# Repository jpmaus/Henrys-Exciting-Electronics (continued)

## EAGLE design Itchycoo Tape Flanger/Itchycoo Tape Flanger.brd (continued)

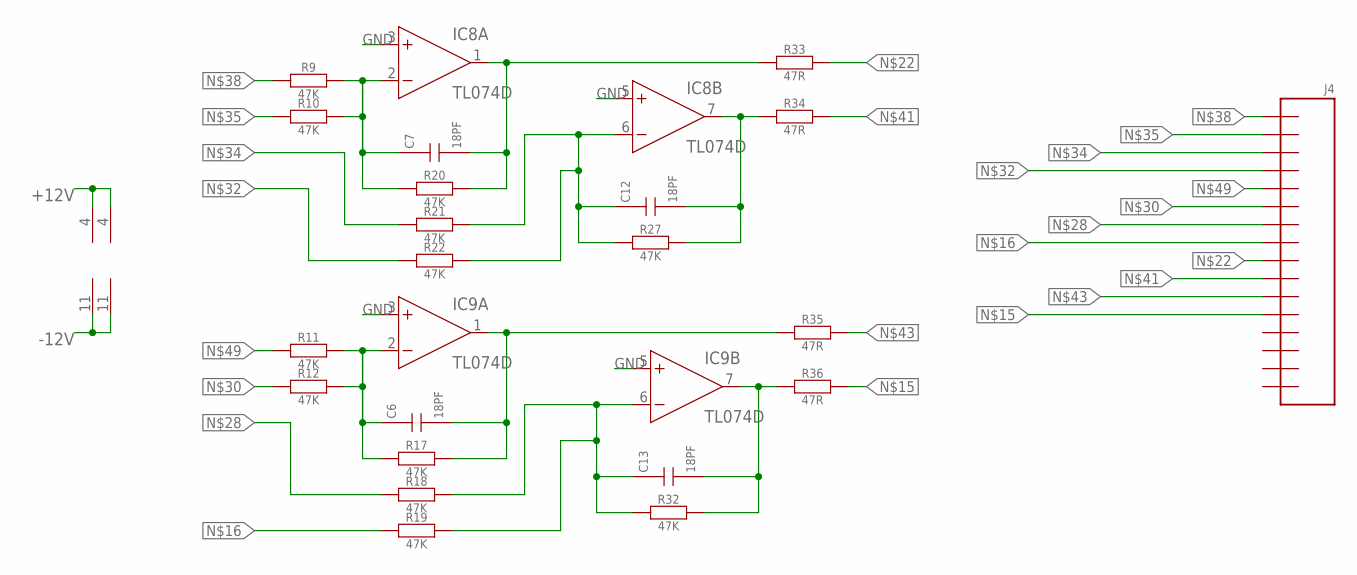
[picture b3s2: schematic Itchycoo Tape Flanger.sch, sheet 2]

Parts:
C6, C7, C12, C13: 18PF; CT6032
IC8, IC9: TL074D; SO14
J4: CON_16; 2X08SMT
R9, R10, R11, R12, R17, R18, R19, R20, R21, R22, R27, R32: 47K; R6332W
R33, R34, R35, R36: 47R; R6332W

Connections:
+12V: IC8.4 (V+), IC9.4 (V+); also elsewhere on the board
-12V: IC8.11 (V-), IC9.11 (V-); also elsewhere on the board
GND: IC8.3 (+IN), IC8.5 (+IN), IC9.3 (+IN), IC9.5 (+IN); also elsewhere on the board
unnamed: J4.12, R36.2
unnamed: J4.8, R19.1
unnamed: J4.9, R33.2
unnamed: J4.7, R18.1
unnamed: J4.6, R12.1
unnamed: J4.4, R22.1
unnamed: J4.3, R21.1
unnamed: J4.2, R10.1
unnamed: C7.+ (1), IC8.2 (-IN), R9.2, R10.2, R20.1
unnamed: C7.- (2), IC8.1 (OUT), R20.2, R33.1
unnamed: J4.1, R9.1
unnamed: C12.- (2), IC8.7 (OUT), R27.2, R34.1
unnamed: J4.10, R34.2
unnamed: J4.11, R35.2
unnamed: J4.5, R11.1
unnamed: C12.+ (1), IC8.6 (-IN), R21.2, R22.2, R27.1
unnamed: C6.+ (1), IC9.2 (-IN), R11.2, R12.2, R17.1
unnamed: C6.- (2), IC9.1 (OUT), R17.2, R35.1
unnamed: C13.- (2), IC9.7 (OUT), R32.2, R36.1
unnamed: C13.+ (1), IC9.6 (-IN), R18.2, R19.2, R32.1

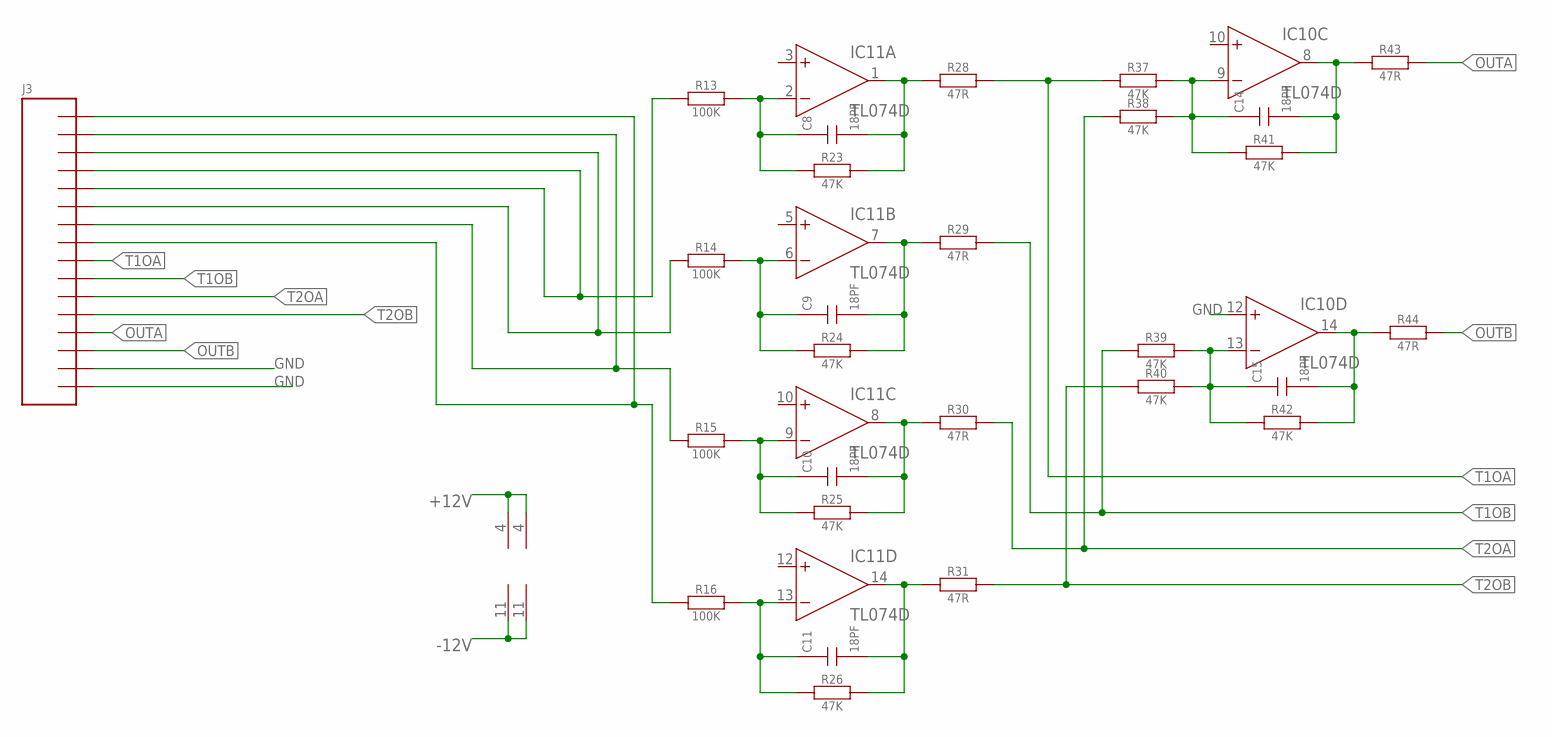
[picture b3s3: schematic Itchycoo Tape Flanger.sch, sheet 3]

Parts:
C8, C9, C10, C11, C14, C15: 18PF; CT6032
IC10, IC11: TL074D; SO14
J3: CON_16; 2X08SMT
R13, R14, R15, R16: 100K; R6332W
R23, R24, R25, R26, R37, R38, R39, R40, R41, R42: 47K; R6332W
R28, R29, R30, R31, R43, R44: 47R; R6332W

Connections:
+12V: IC10.4 (V+), IC11.4 (V+); also elsewhere on the board
-12V: IC10.11 (V-), IC11.11 (V-); also elsewhere on the board
GND: IC10.12 (+IN), J3.15, J3.16; also elsewhere on the board
unnamed: J3.4, J3.5, R13.1
unnamed: C8.- (2), IC11.1 (OUT), R23.2, R28.1
unnamed: J3.3, J3.6, R14.1
unnamed: J3.2, J3.7, R15.1
unnamed: J3.1, J3.8, R16.1
unnamed: C9.+ (1), IC11.6 (-IN), R14.2, R24.1
unnamed: C9.- (2), IC11.7 (OUT), R24.2, R29.1
unnamed: C10.+ (1), IC11.9 (-IN), R15.2, R25.1
unnamed: C10.- (2), IC11.8 (OUT), R25.2, R30.1
unnamed: C11.- (2), IC11.14 (OUT), R26.2, R31.1
unnamed: C11.+ (1), IC11.13 (-IN), R16.2, R26.1
unnamed: C8.+ (1), IC11.2 (-IN), R13.2, R23.1
unnamed: C14.+ (1), IC10.9 (-IN), R37.2, R38.2, R41.1
unnamed: C14.- (2), IC10.8 (OUT), R41.2, R43.1
unnamed: C15.+ (1), IC10.13 (-IN), R39.2, R40.2, R42.1
unnamed: C15.- (2), IC10.14 (OUT), R42.2, R44.1
OUTA: J3.13, R43.2
OUTB: J3.14, R44.2
T1OA: J3.9, R28.2, R37.1
T1OB: J3.10, R29.2, R39.1
T2OA: J3.11, R30.2, R38.1
T2OB: J3.12, R31.2, R40.1

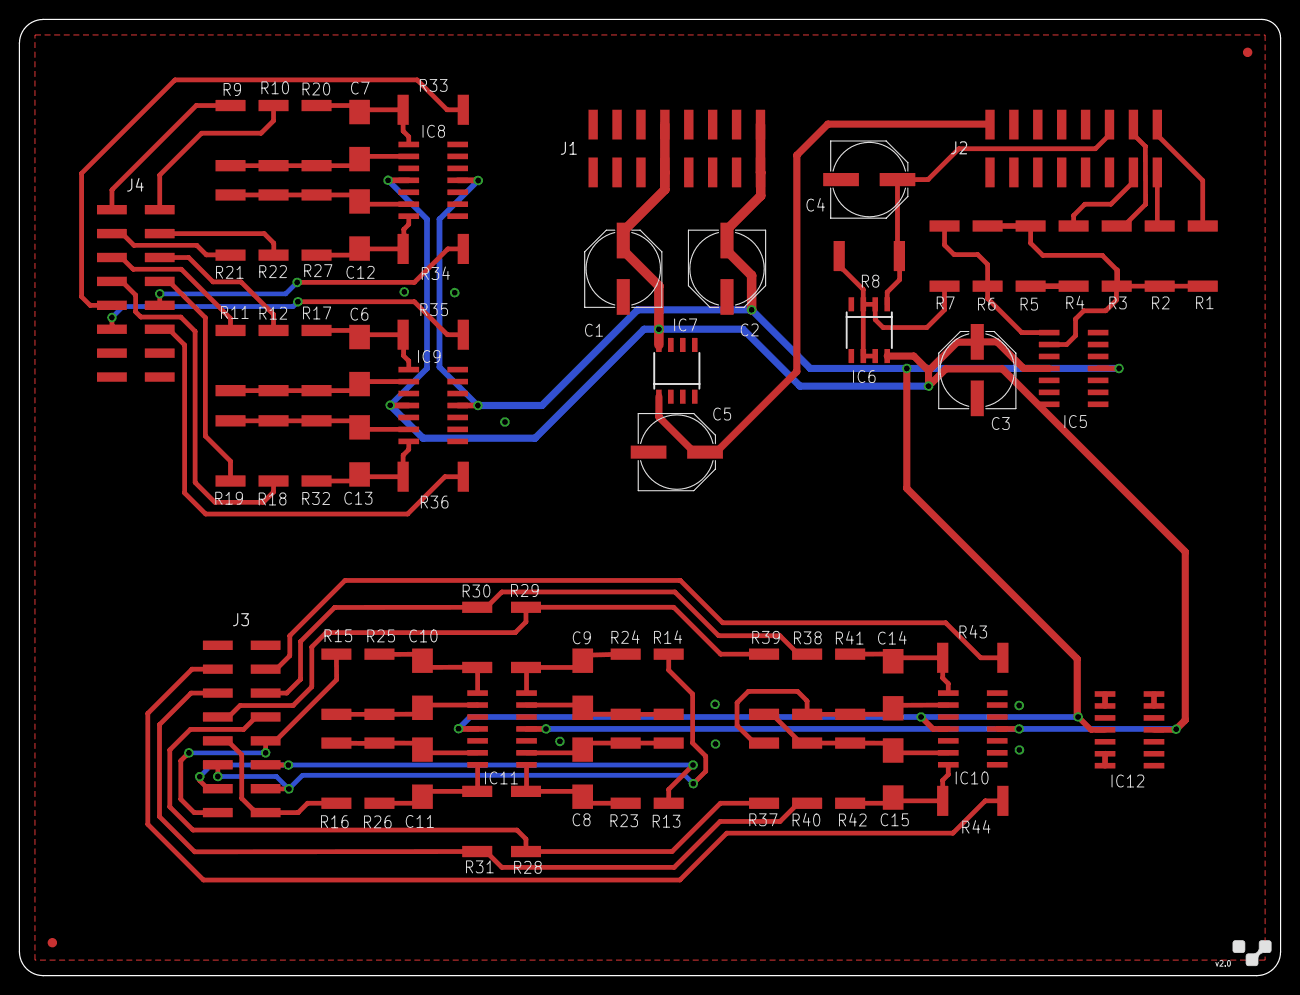
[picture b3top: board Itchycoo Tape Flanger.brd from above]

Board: 2 copper layers, 134.0 x 101.6 mm, 72 parts (0 on the bottom side), 58 nets.

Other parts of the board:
E$1: 4X5_BOARD_V2

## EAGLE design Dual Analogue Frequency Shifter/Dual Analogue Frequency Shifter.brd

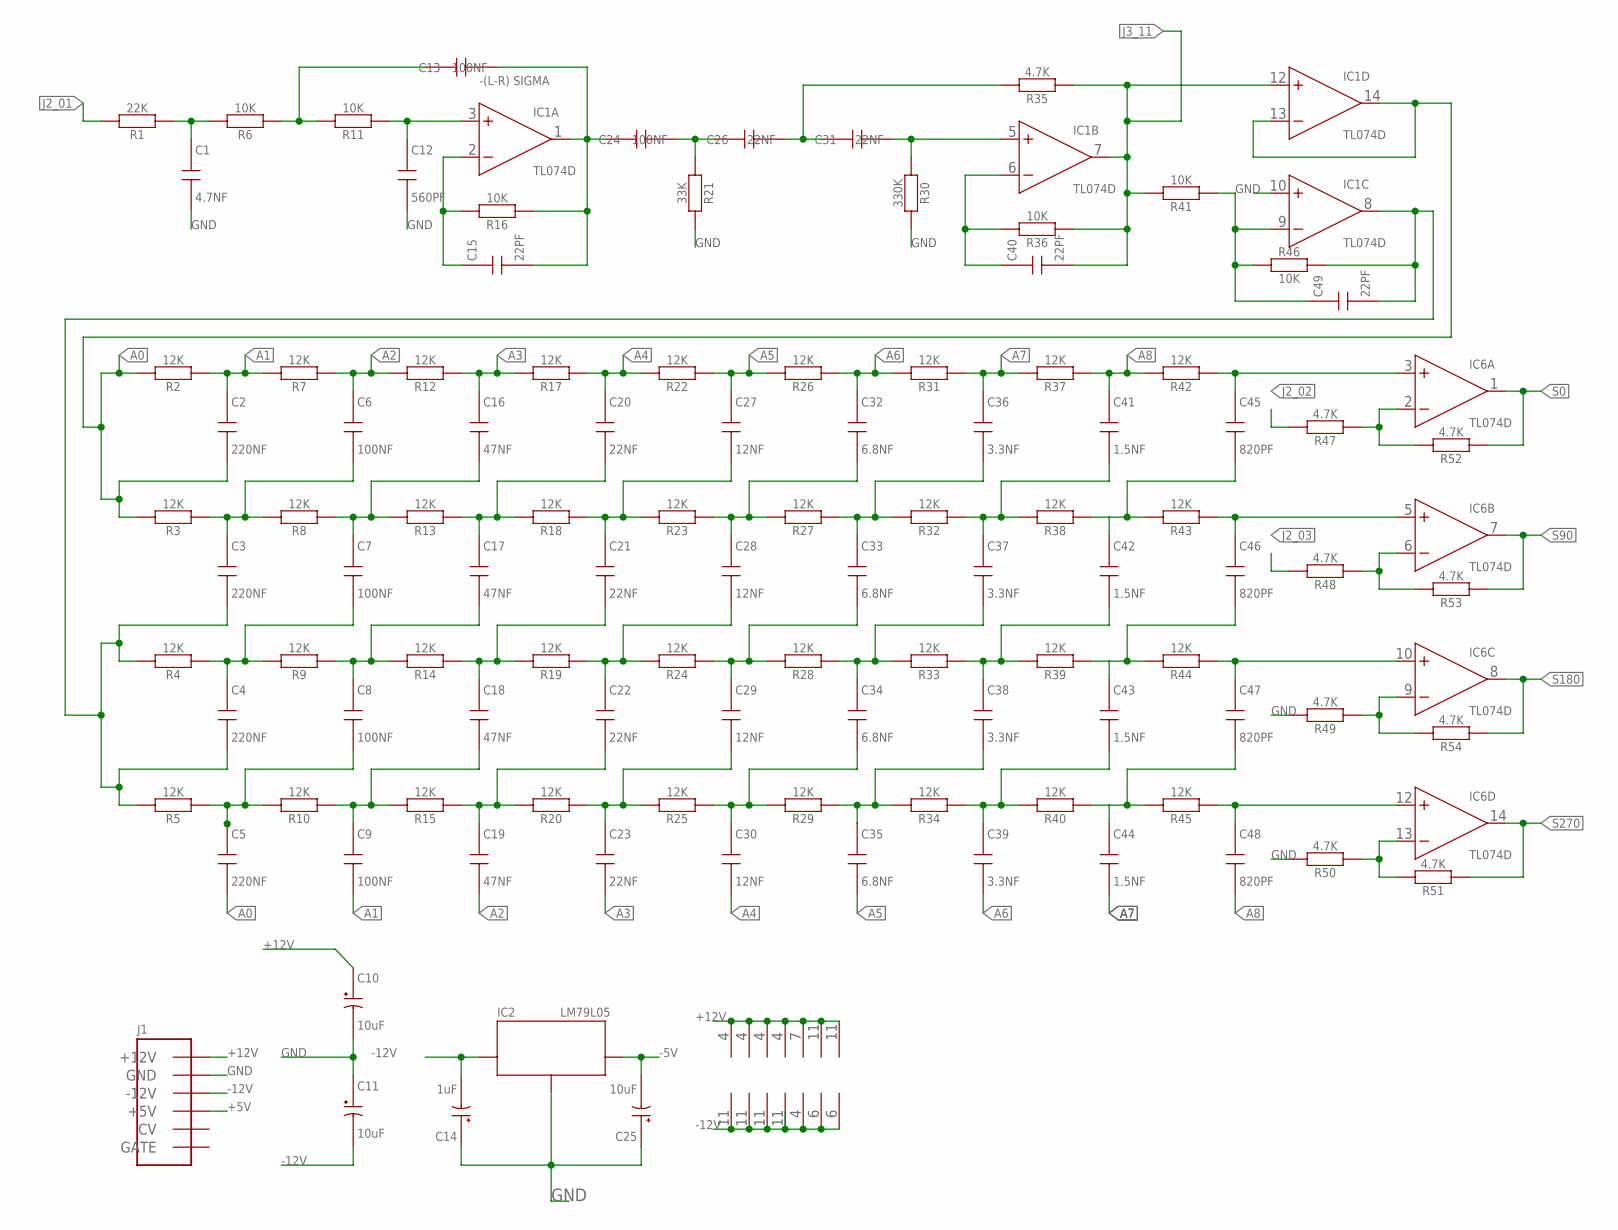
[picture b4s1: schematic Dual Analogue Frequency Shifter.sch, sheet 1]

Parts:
C1: 4.7NF; CT6032
C2, C3, C4, C5: 220NF; CT6032
C6, C7, C8, C9, C13, C24: 100NF; CT6032
C10, C11, C25: 10uF; PANASONIC_E
C12: 560PF; CT6032
C14: 1uF; PANASONIC_E
C15, C40, C49: 22PF; CT6032
C16, C17, C18, C19: 47NF; CT6032
C20, C21, C22, C23, C26, C31: 22NF; CT6032
C27, C28, C29, C30: 12NF; CT6032
C32, C33, C34, C35: 6.8NF; CT6032
C36, C37, C38, C39: 3.3NF; CT6032
C41, C42, C43, C44: 1.5NF; CT6032
C45, C46, C47, C48: 820PF; CT6032
IC1, IC4, IC6: TL074D; SO14
IC2: LM79L05; SO08
IC3: OPA4277U; SO14
IC5: OP1177; SO08
IC7, IC8: LM13700; SO16
J1: EURO; 2X08SMT
R1: 22K; R6332W
R2, R3, R4, R5, R7, R8, R9, R10, R12, R13, R14, R15, R17, R18, R19, R20, R22, R23, R24, R25, R26, R27, R28, R29, R31, R32, R33, R34, R37, R38, R39, R40, R42, R43, R44, R45: 12K; R6332W
R6, R11, R16, R36, R41, R46: 10K; R6332W
R21: 33K; R6332W
R30: 330K; R6332W
R35, R47, R48, R49, R50, R51, R52, R53, R54: 4.7K; R6332W

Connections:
+5V: J1.11 (+5V), J1.12 (+5V); also elsewhere on the board
+12V: C10.+ (1), IC1.4 (V+), IC3.4 (V+), IC4.4 (V+), IC5.7 (V+), IC6.4 (V+), IC7.11 (V+), IC8.11 (V+), J1.9 (+12V), J1.10 (+12V); also elsewhere on the board
-5V: C25.- (2), IC2.1 (OUT); also elsewhere on the board
-12V: C11.- (2), C14.- (2), IC1.11 (V-), IC2.8 (IN), IC3.11 (V-), IC4.11 (V-), IC5.4 (V-), IC6.11 (V-), IC7.6 (V-), IC8.6 (V-), J1.1 (-12V), J1.2 (-12V); also elsewhere on the board
A0: C2.- (2), C5.- (2), IC1.13 (-IN), IC1.14 (OUT), R2.2, R3.2
A1: C2.+ (1), C9.- (2), R2.1, R7.2
A2: C6.+ (1), C19.- (2), R7.1, R12.2
A3: C16.+ (1), C23.- (2), R12.1, R17.2
A4: C20.+ (1), C30.- (2), R17.1, R22.2
A5: C27.+ (1), C35.- (2), R22.1, R26.2
A6: C32.+ (1), C39.- (2), R26.1, R31.2
A7: C36.+ (1), C44.- (2), R31.1, R37.2
A8: C41.+ (1), C48.- (2), R37.1, R42.2
GND: C1.- (2), C10.- (2), C11.+ (1), C12.- (2), C14.+ (1), C25.+ (1), IC1.10 (+IN), IC2.2 (GND), IC2.3 (GND), IC2.6 (GND), IC2.7 (GND), J1.3 (GND), J1.4 (GND), J1.5 (GND), J1.6 (GND), J1.7 (GND), J1.8 (GND), R21.2, R30.2, R49.2, R50.2; also elsewhere on the board
J2_01: R1.2; also elsewhere on the board
J2_02: R47.2; also elsewhere on the board
J2_03: R48.2; also elsewhere on the board
J3_11: C40.- (2), IC1.7 (OUT), IC1.12 (+IN), R35.1, R36.1, R41.2; also elsewhere on the board
unnamed: C35.+ (1), C38.- (2), R29.1, R34.2
unnamed: C3.+ (1), C6.- (2), R3.1, R8.2
unnamed: C7.+ (1), C16.- (2), R8.1, R13.2
unnamed: C17.+ (1), C20.- (2), R13.1, R18.2
unnamed: C21.+ (1), C27.- (2), R18.1, R23.2
unnamed: C28.+ (1), C32.- (2), R23.1, R27.2
unnamed: C33.+ (1), C36.- (2), R27.1, R32.2
unnamed: C37.+ (1), C41.- (2), R32.1, R38.2
unnamed: C4.+ (1), C7.- (2), R4.1, R9.2
unnamed: C8.+ (1), C17.- (2), R9.1, R14.2
unnamed: C18.+ (1), C21.- (2), R14.1, R19.2
unnamed: C22.+ (1), C28.- (2), R19.1, R24.2
unnamed: C29.+ (1), C33.- (2), R24.1, R28.2
unnamed: C34.+ (1), C37.- (2), R28.1, R33.2
unnamed: C38.+ (1), C42.- (2), R33.1, R39.2
unnamed: C5.+ (1), C8.- (2), R5.1, R10.2
unnamed: C9.+ (1), C18.- (2), R10.1, R15.2
unnamed: C19.+ (1), C22.- (2), R15.1, R20.2
unnamed: C23.+ (1), C29.- (2), R20.1, R25.2
unnamed: C30.+ (1), C34.- (2), R25.1, R29.2
unnamed: C39.+ (1), C43.- (2), R34.1, R40.2
unnamed: C1.+ (1), R1.1, R6.2
unnamed: C13.+ (1), R6.1, R11.2
unnamed: C12.+ (1), IC1.3 (+IN), R11.1
unnamed: C31.- (2), IC1.5 (+IN), R30.1
unnamed: C13.- (2), C15.- (2), C24.+ (1), IC1.1 (OUT), R16.1
unnamed: C15.+ (1), IC1.2 (-IN), R16.2
unnamed: C24.- (2), C26.+ (1), R21.1
unnamed: IC6.2 (-IN), R47.1, R52.2
unnamed: C3.- (2), C4.- (2), C49.- (2), IC1.8 (OUT), R4.2, R5.2, R46.2
unnamed: IC6.6 (-IN), R48.1, R53.2
unnamed: C49.+ (1), IC1.9 (-IN), R41.1, R46.1
unnamed: C26.- (2), C31.+ (1), R35.2
unnamed: C42.+ (1), C45.- (2), R38.1, R43.2
unnamed: IC6.9 (-IN), R49.1, R54.2
unnamed: C43.+ (1), C46.- (2), R39.1, R44.2
unnamed: IC6.13 (-IN), R50.1, R51.2
unnamed: C40.+ (1), IC1.6 (-IN), R36.2
unnamed: C44.+ (1), C47.- (2), R40.1, R45.2
unnamed: C45.+ (1), IC6.3 (+IN), R42.1
unnamed: C46.+ (1), IC6.5 (+IN), R43.1
unnamed: C48.+ (1), IC6.12 (+IN), R45.1
unnamed: C47.+ (1), IC6.10 (+IN), R44.1
S0: IC6.1 (OUT), R52.1
S90: IC6.7 (OUT), R53.1
S180: IC6.8 (OUT), R54.1
S270: IC6.14 (OUT), R51.1

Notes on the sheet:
-(L-R) SIGMA

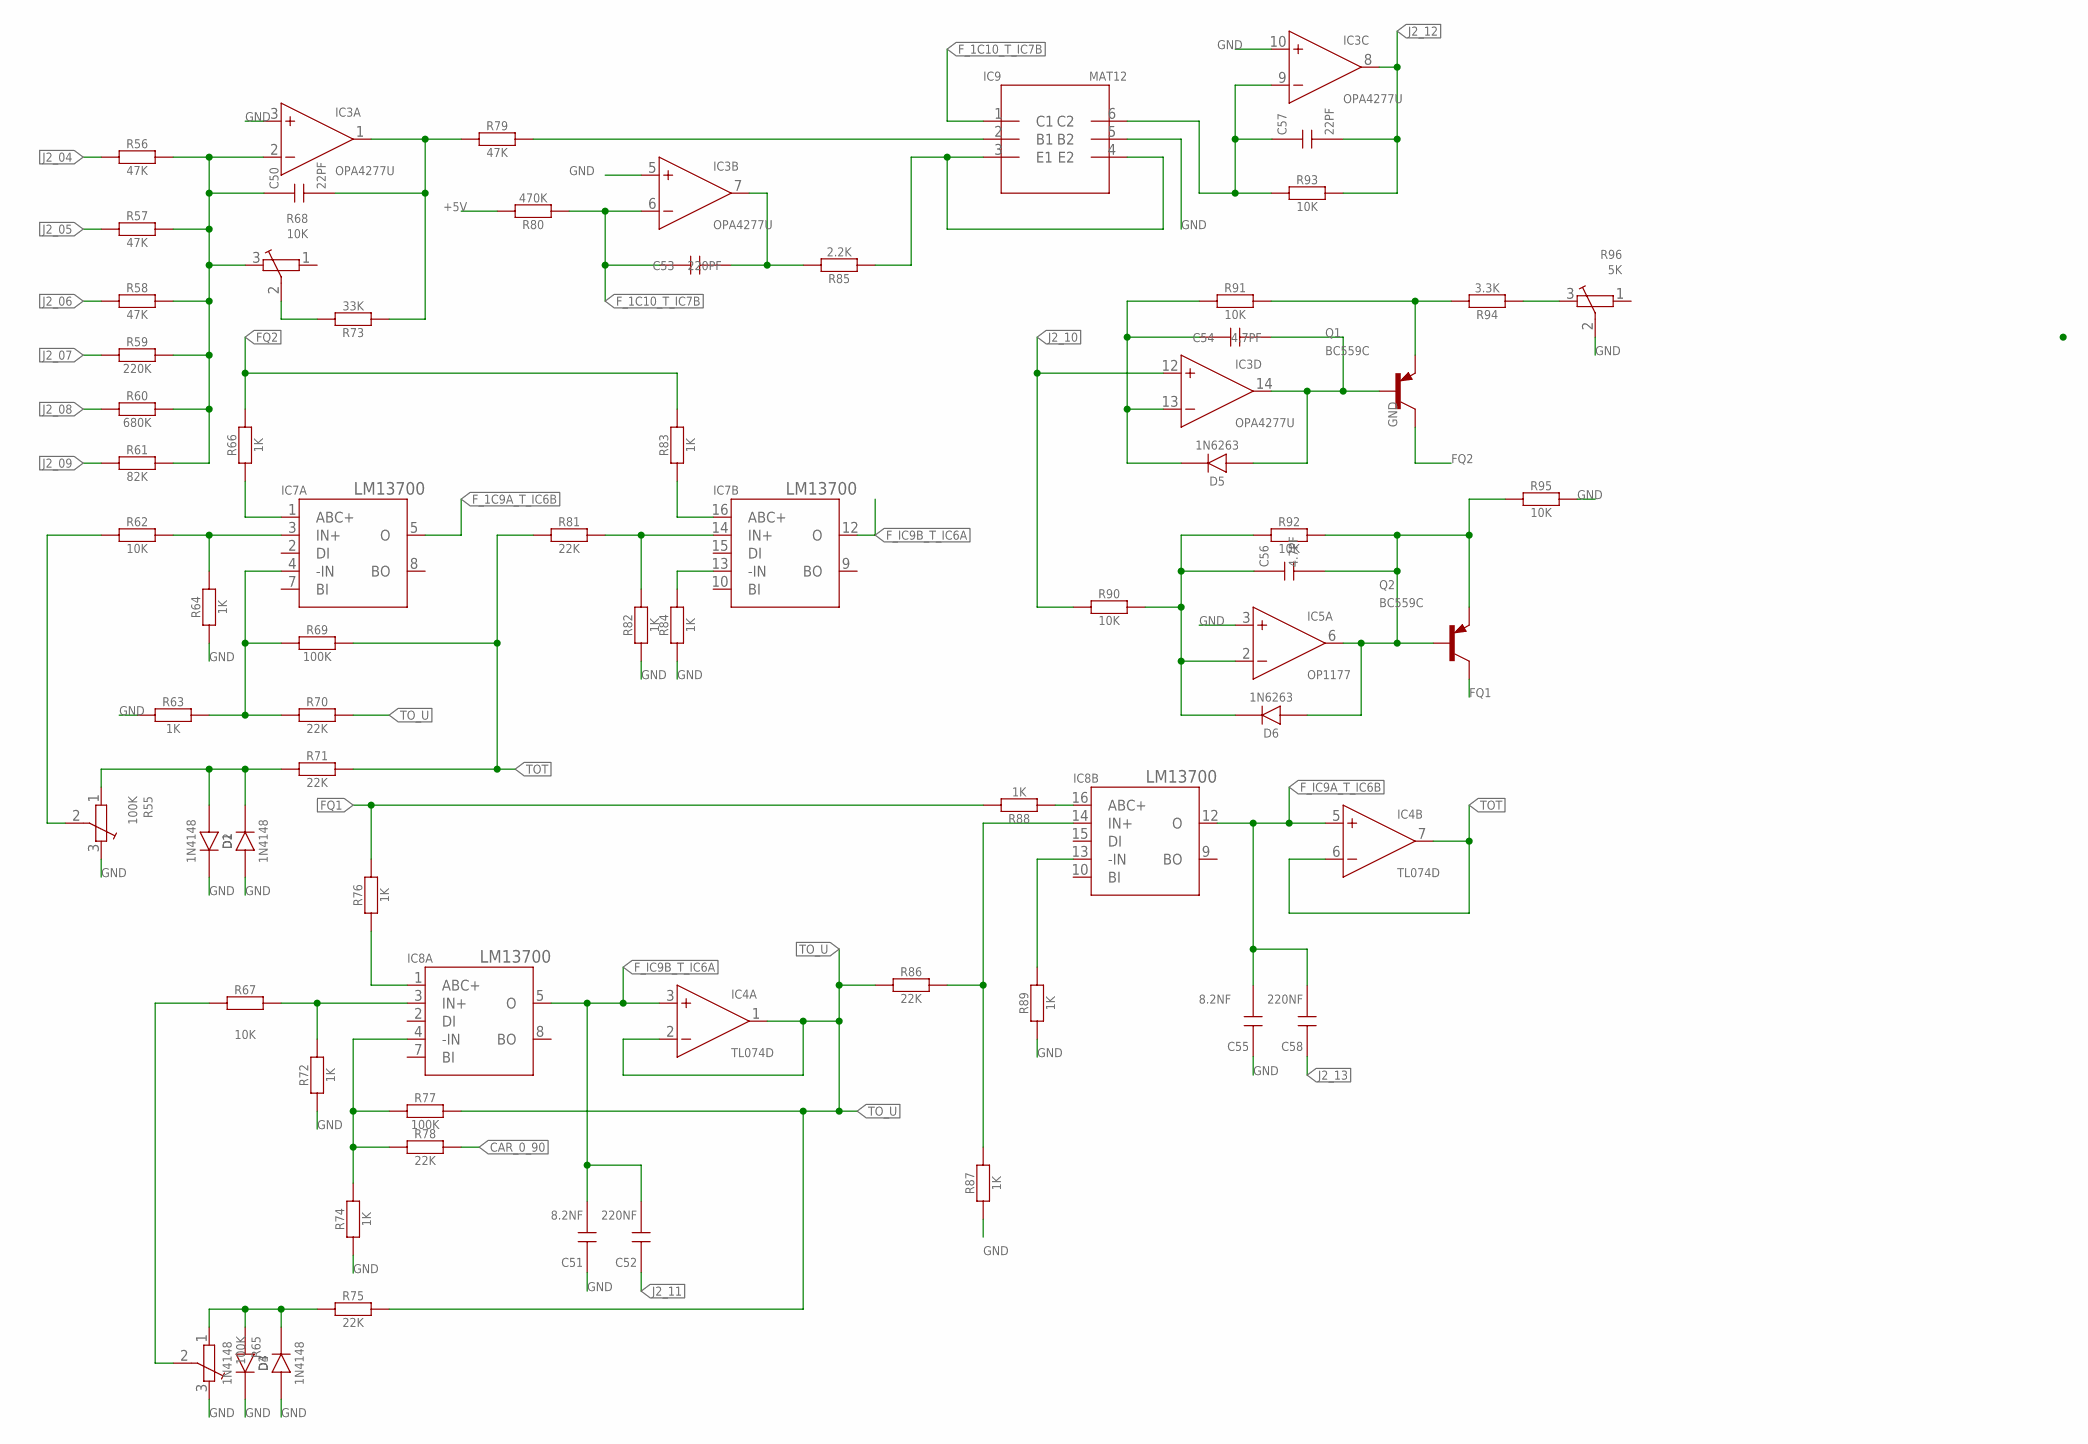
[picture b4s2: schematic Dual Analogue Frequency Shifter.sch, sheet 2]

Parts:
C50, C57: 22PF; CT6032
C51, C55: 8.2NF; CT6032
C52, C58: 220NF; CT6032
C53: 220PF; CT6032
C54, C56: 4.7PF; CT6032
D1, D2, D3, D4: 1N4148; SOD123
D5, D6: 1N6263; SOD123
IC3: OPA4277U; SO14
IC4: TL074D; SO14
IC5: OP1177; SO08
IC7, IC8: LM13700; SO16
IC9: MAT12; H_6
Q1, Q2: BC559C; TO92
R55, R65: 100K; TRIM
R56, R57, R58, R79: 47K; R6332W
R59: 220K; R6332W
R60: 680K; R6332W
R61: 82K; R6332W
R62, R67, R90, R91, R92, R93, R95: 10K; R6332W
R63, R64, R66, R72, R74, R76, R82, R83, R84, R87, R88, R89: 1K; R6332W
R68: 10K; TRIM
R69, R77: 100K; R6332W
R70, R71, R75, R78, R81, R86: 22K; R6332W
R73: 33K; R6332W
R80: 470K; R6332W
R85: 2.2K; R6332W
R94: 3.3K; R6332W
R96: 5K; TRIM

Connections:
+5V: R80.2; also elsewhere on the board
CAR_0_90: R78.2; also elsewhere on the board
FQ1: Q2.C, R76.2, R88.2
FQ2: Q1.C, R66.2, R83.2
F_1C9A_T_IC6B: IC7.5 (O)
F_1C10_T_IC7B: C53.+ (1), IC3.6 (-IN), IC9.1 (C1), R80.1
F_IC9A_T_IC6B: C55.- (2), C58.- (2), IC4.5 (+IN), IC8.12 (O)
F_IC9B_T_IC6A: C51.- (2), C52.- (2), IC4.3 (+IN), IC7.12 (O), IC8.5 (O)
GND: C51.+ (1), C55.+ (1), D1.C, D2.A, D3.C, D4.A, IC3.3 (+IN), IC3.5 (+IN), IC3.10 (+IN), IC5.3 (+IN), IC9.5 (B2), R55.3, R63.1, R64.1, R65.3, R72.1, R74.1, R82.1, R84.1, R87.1, R89.1, R95.2, R96.2; also elsewhere on the board
J2_04: R56.1; also elsewhere on the board
J2_05: R57.1; also elsewhere on the board
J2_06: R58.1; also elsewhere on the board
J2_07: R59.1; also elsewhere on the board
J2_08: R60.1; also elsewhere on the board
J2_09: R61.1; also elsewhere on the board
J2_10: IC3.12 (+IN), R90.1; also elsewhere on the board
J2_11: C52.+ (1); also elsewhere on the board
J2_12: C57.- (2), IC3.8 (OUT), R93.2; also elsewhere on the board
J2_13: C58.+ (1); also elsewhere on the board
unnamed: R94.1, R96.3
unnamed: IC9.3 (E1), IC9.4 (E2), R85.1
unnamed: C50.+ (1), IC3.2 (-IN), R56.2, R57.2, R58.2, R59.2, R60.2, R61.2, R68.3
unnamed: C50.- (2), IC3.1 (OUT), R73.1, R79.1
unnamed: C53.- (2), IC3.7 (OUT), R85.2
unnamed: IC9.2 (B1), R79.2
unnamed: C57.+ (1), IC3.9 (-IN), IC9.6 (C2), R93.1
unnamed: C54.+ (1), D5.C, IC3.13 (-IN), R91.1
unnamed: C54.- (2), D5.A, IC3.14 (OUT), Q1.B
unnamed: Q1.E, R91.2, R94.2
unnamed: C56.+ (1), D6.C, IC5.2 (-IN), R90.2, R92.1
unnamed: C56.- (2), D6.A, IC5.6 (OUT), Q2.B, Q2.E, R92.2, R95.1
unnamed: D3.A, D4.C, R65.1, R75.1
unnamed: IC8.3 (IN+), R67.2, R72.2
unnamed: IC8.1 (ABC+), R76.1
unnamed: IC8.4 (-IN), R74.2, R77.1, R78.1
unnamed: IC8.16 (ABC+), R88.1
unnamed: IC8.14 (IN+), R86.2, R87.2
unnamed: IC8.13 (-IN), R89.2
unnamed: IC7.3 (IN+), R62.2, R64.2
unnamed: IC7.4 (-IN), R63.2, R69.1, R70.1
unnamed: IC7.1 (ABC+), R66.1
unnamed: IC7.16 (ABC+), R83.1
unnamed: IC7.13 (-IN), R84.2
unnamed: IC7.14 (IN+), R81.2, R82.2
unnamed: D1.A, D2.C, R55.1, R71.1
unnamed: R68.2, R73.2
unnamed: R65.2, R67.1
unnamed: R55.2, R62.1
TOT: IC4.6 (-IN), IC4.7 (OUT), R69.2, R71.2, R81.1
TO_U: IC4.1 (OUT), IC4.2 (-IN), R70.2, R75.2, R77.2, R86.1

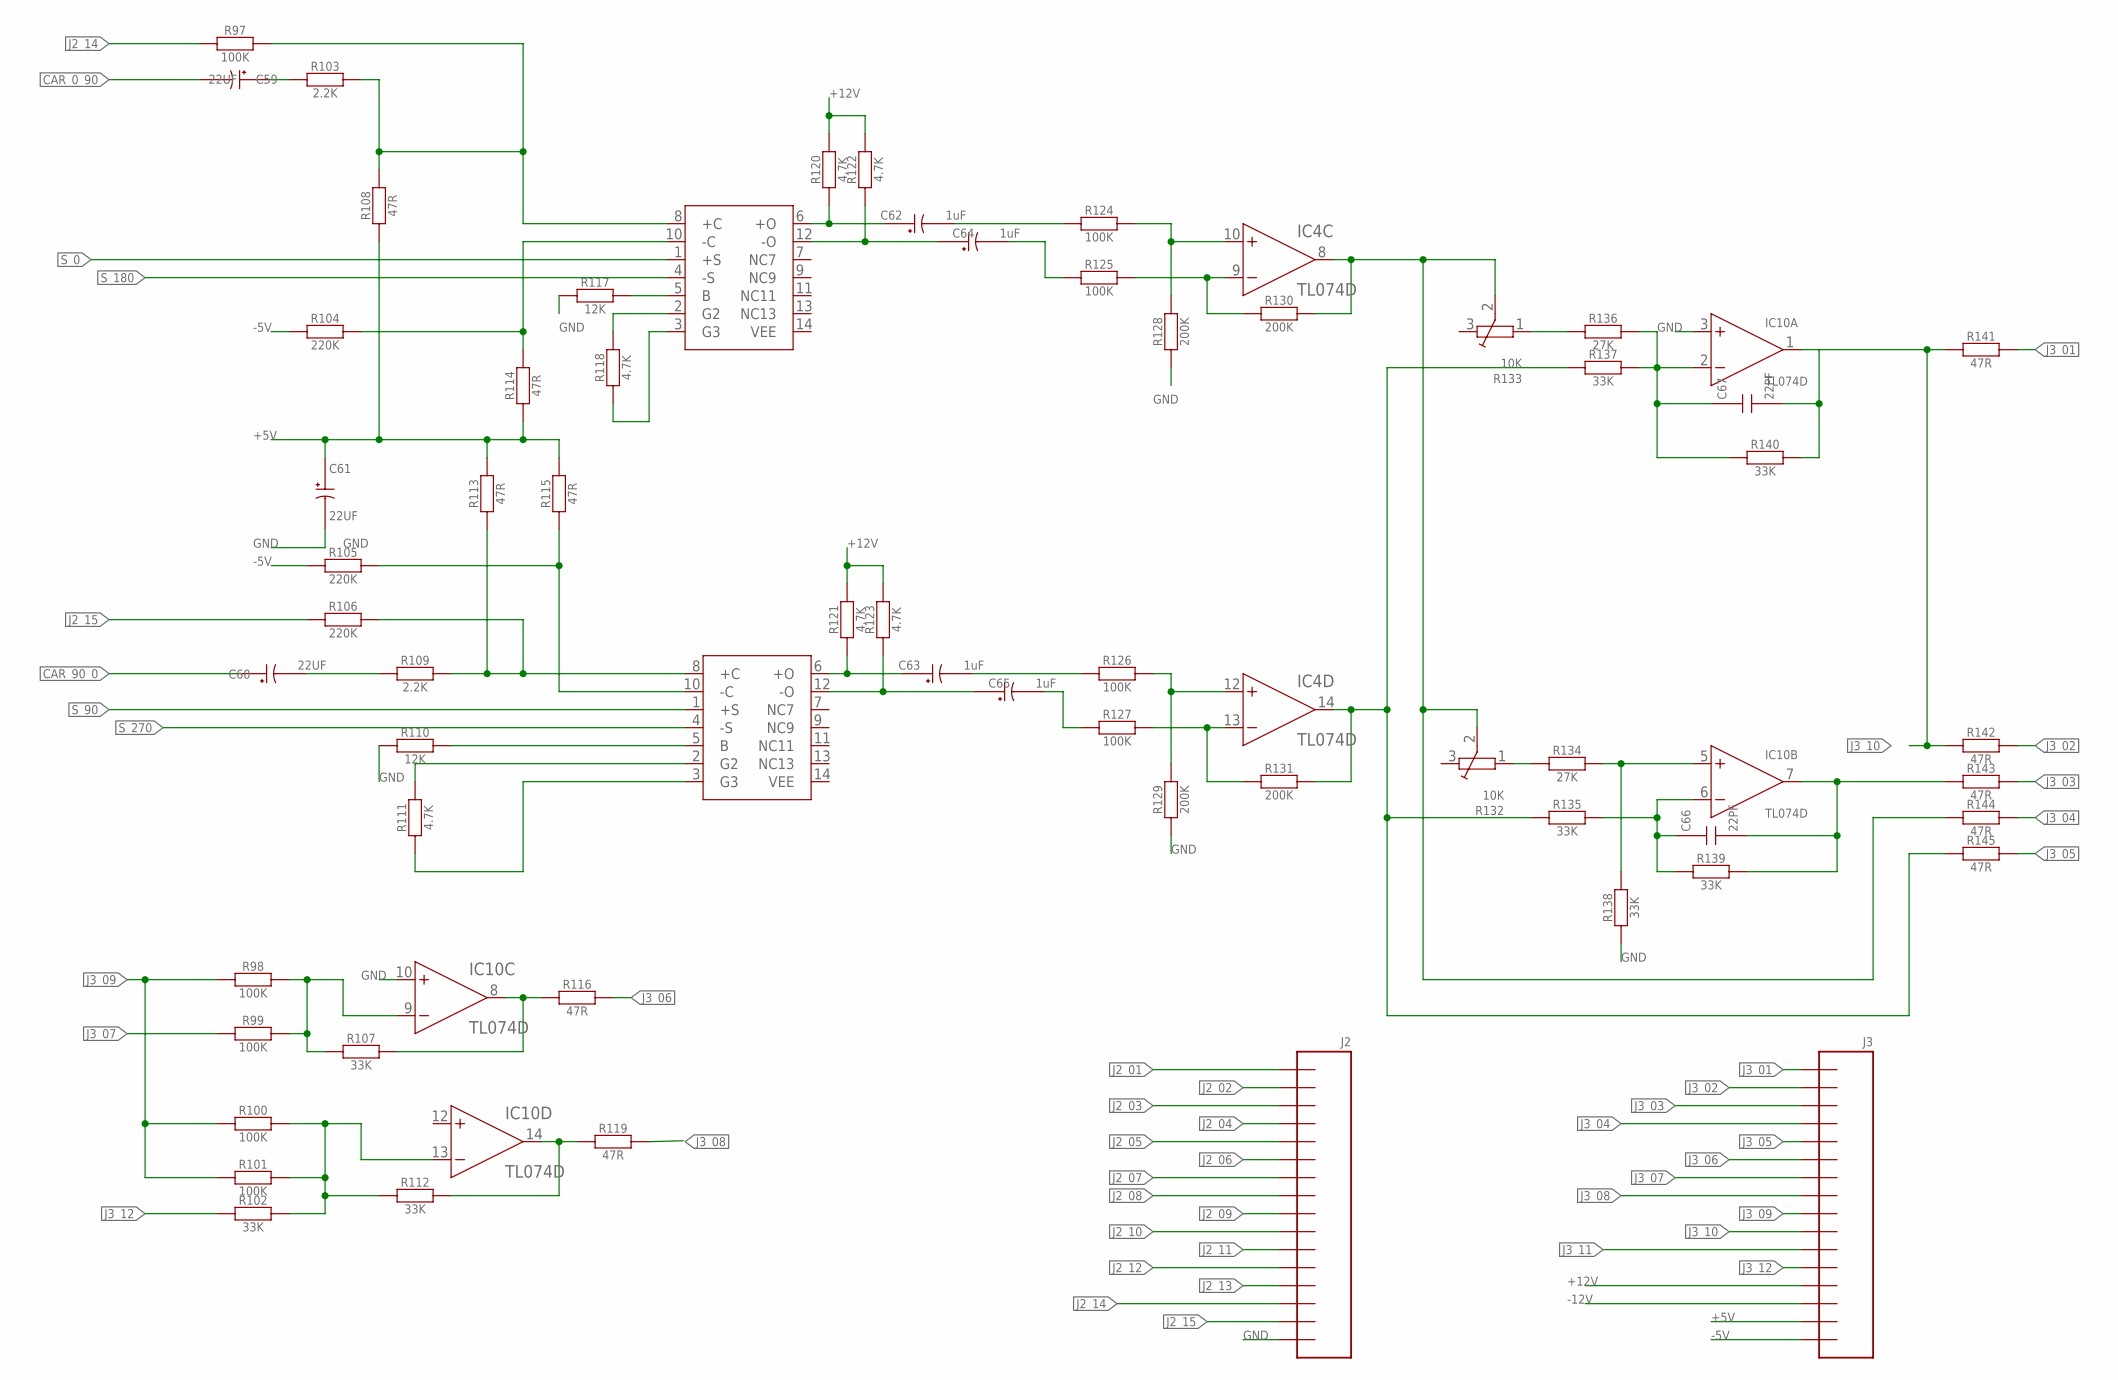
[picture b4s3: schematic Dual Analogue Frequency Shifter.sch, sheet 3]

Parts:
C59, C60, C61: 22UF; PANASONIC_E
C62, C63, C64, C65: 1uF; PANASONIC_E
C66, C67: 22PF; CT6032
IC4, IC10: TL074D; SO14
J2, J3: CON_16; 2X08SMT
R97, R98, R99, R100, R101, R124, R125, R126, R127: 100K; R6332W
R102, R107, R112, R135, R137, R138, R139, R140: 33K; R6332W
R103, R109: 2.2K; R6332W
R104, R105, R106: 220K; R6332W
R108, R113, R114, R115, R116, R119, R141, R142, R143, R144, R145: 47R; R6332W
R110, R117: 12K; R6332W
R111, R118, R120, R121, R122, R123: 4.7K; R6332W
R128, R129, R130, R131: 200K; R6332W
R132, R133: 10K; TRIM
R134, R136: 27K; R6332W
U1, U2: MC1496; SO14

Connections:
+5V: C61.+ (1), J3.15, R108.1, R113.2, R114.1, R115.2; also elsewhere on the board
+12V: IC10.4 (V+), J3.13, R120.2, R121.2, R122.2, R123.2; also elsewhere on the board
-5V: J3.16, R104.1, R105.1; also elsewhere on the board
-12V: IC10.11 (V-), J3.14; also elsewhere on the board
CAR_0_90: C59.- (2); also elsewhere on the board
CAR_90_0: C60.+ (1)
GND: C61.- (2), IC10.3 (+IN), IC10.10 (+IN), J2.16, R110.1, R117.1, R128.1, R129.1, R138.1; also elsewhere on the board
J2_01: J2.1; also elsewhere on the board
J2_02: J2.2; also elsewhere on the board
J2_03: J2.3; also elsewhere on the board
J2_04: J2.4; also elsewhere on the board
J2_05: J2.5; also elsewhere on the board
J2_06: J2.6; also elsewhere on the board
J2_07: J2.7; also elsewhere on the board
J2_08: J2.8; also elsewhere on the board
J2_09: J2.9; also elsewhere on the board
J2_10: J2.10; also elsewhere on the board
J2_11: J2.11; also elsewhere on the board
J2_12: J2.12; also elsewhere on the board
J2_13: J2.13; also elsewhere on the board
J2_14: J2.14, R97.1
J2_15: J2.15, R106.1
J3_01: J3.1, R141.2
J3_02: J3.2, R142.2
J3_03: J3.3, R143.2
J3_04: J3.4, R144.2
J3_05: J3.5, R145.2
J3_06: J3.6, R116.2
J3_07: J3.7, R99.1
J3_08: J3.8, R119.2
J3_09: J3.9, R98.1, R100.1, R101.1
J3_10: C67.- (2), IC10.1 (OUT), J3.10, R140.2, R141.1, R142.1
J3_11: J3.11; also elsewhere on the board
J3_12: J3.12, R102.1
J201: R132.1, R134.1
unnamed: IC4.14 (OUT), R131.2, R135.1, R137.1, R145.1
unnamed: IC10.9 (-IN), R98.2, R99.2, R107.1
unnamed: IC10.8 (OUT), R107.2, R116.1
unnamed: IC10.13 (-IN), R100.2, R101.2, R102.2, R112.1
unnamed: IC10.14 (OUT), R112.2, R119.1
unnamed: R97.2, R103.2, R108.2, U1.8 (+C)
unnamed: C59.+ (1), R103.1
unnamed: R104.2, R114.2, U1.10 (-C)
unnamed: R105.2, R115.1, U2.10 (-C)
unnamed: C60.- (2), R109.1
unnamed: R106.2, R109.2, R113.1, U2.8 (+C)
unnamed: R110.2, U2.5 (B)
unnamed: R117.2, U1.5 (B)
unnamed: R118.2, U1.2 (G2)
unnamed: R111.2, U2.2 (G2)
unnamed: R111.1, U2.3 (G3)
unnamed: R118.1, U1.3 (G3)
unnamed: C62.+ (1), R120.1, U1.6 (+O)
unnamed: C64.+ (1), R122.1, U1.12 (-O)
unnamed: C62.- (2), R124.1
unnamed: C64.- (2), R125.1
unnamed: IC4.10 (+IN), R124.2, R128.2
unnamed: C63.+ (1), R121.1, U2.6 (+O)
unnamed: C65.+ (1), R123.1, U2.12 (-O)
unnamed: C63.- (2), R126.1
unnamed: C65.- (2), R127.1
unnamed: IC4.12 (+IN), R126.2, R129.2
unnamed: IC4.9 (-IN), R125.2, R130.1
unnamed: IC4.13 (-IN), R127.2, R131.1
unnamed: IC4.8 (OUT), R130.2, R132.2, R133.2, R144.1
unnamed: IC10.5 (+IN), R134.2, R138.2
unnamed: C67.+ (1), IC10.2 (-IN), R136.2, R137.2, R140.1
unnamed: R133.1, R136.1
unnamed: C66.+ (1), IC10.6 (-IN), R135.2, R139.1
unnamed: C66.- (2), IC10.7 (OUT), R139.2, R143.1
S_0: U1.1 (+S)
S_90: U2.1 (+S)
S_180: U1.4 (-S)
S_270: U2.4 (-S)
VEE: U1.14 (VEE), U2.14 (VEE)

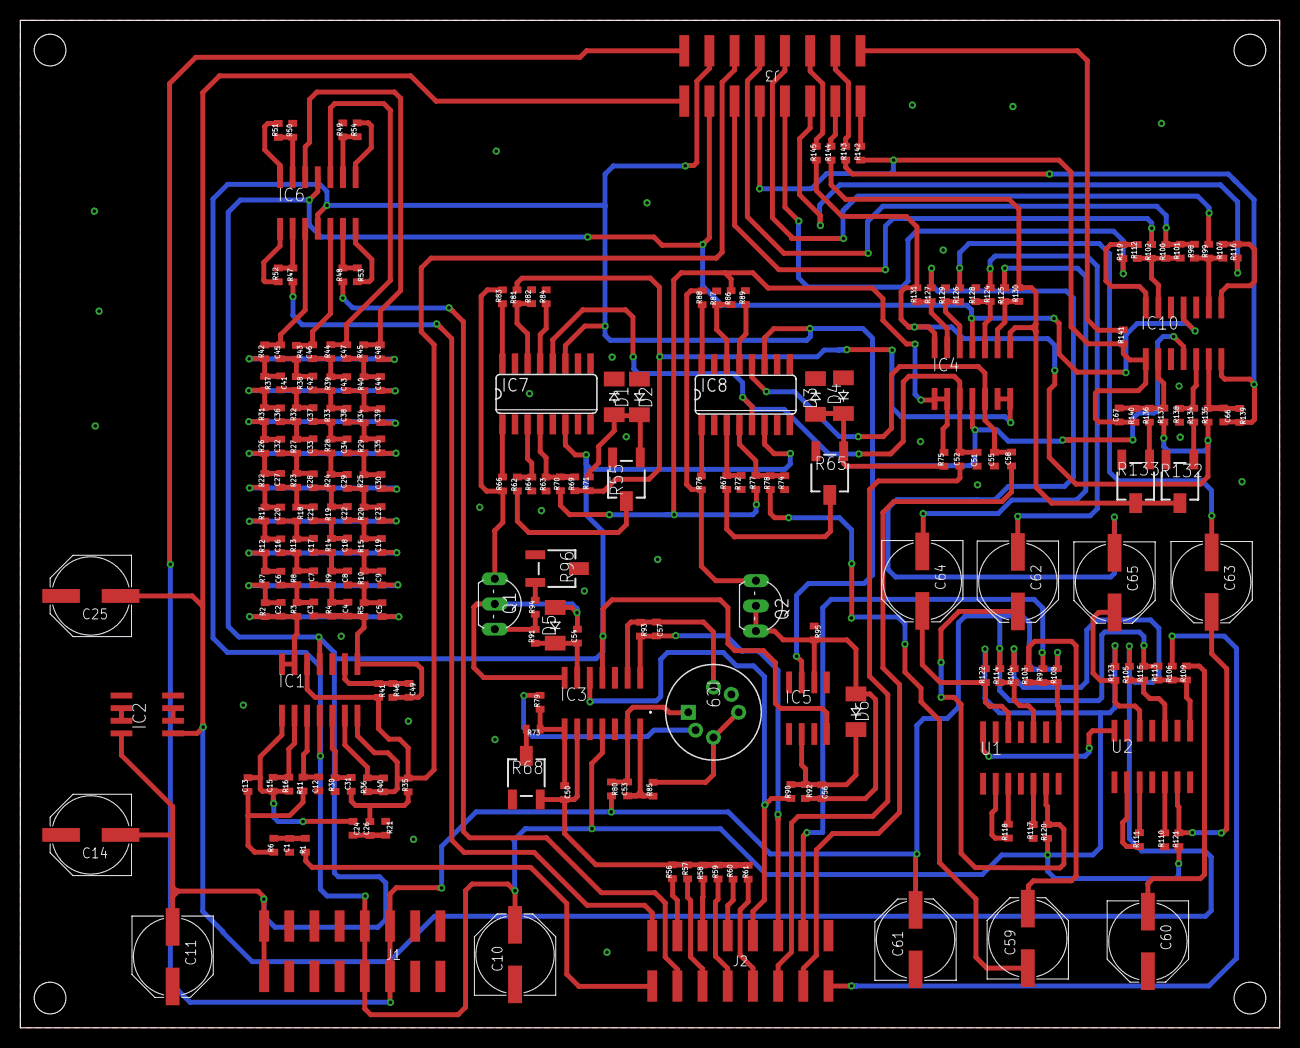
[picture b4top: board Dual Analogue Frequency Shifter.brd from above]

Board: 2 copper layers, 127.0 x 101.6 mm, 235 parts (0 on the bottom side), 162 nets.
